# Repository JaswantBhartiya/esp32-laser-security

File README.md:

<div align="center">

  <br><br>

<br><br>

# 🛡️ ESP32 Multi-Bounce Laser Security System
<!-- Badges Section -->
<p align="center">

</p>

<h4>
    <a href="#demo">Demo</a>&nbsp;&nbsp;&nbsp;&nbsp;•&nbsp;&nbsp;&nbsp;&nbsp;
    <a href="#hardware">Hardware Design</a>&nbsp;&nbsp;&nbsp;&nbsp;•&nbsp;&nbsp;&nbsp;&nbsp;
    <a href="#mechanical">Mechanical Shroud</a>&nbsp;&nbsp;&nbsp;&nbsp;•&nbsp;&nbsp;&nbsp;&nbsp;
    <a href="#firmware">Firmware & Calibration</a>&nbsp;&nbsp;&nbsp;&nbsp;•&nbsp;&nbsp;&nbsp;&nbsp;
    <a href="https://github.com/JaswantBhartiya" target="_blank">Contact</a>
</h4>
</div>

<br>

A professional, budget-friendly embedded security system built around a custom PCB and the ESP32 DevKit V1. This project utilizes an optical multi-bounce laser path bounced across real glass mirrors to form a tight perimeter grid, monitored dynamically by an onboard Light Dependent Resistor (LDR).

<br><br>

---

## <span id="demo">🚀</span> Key Features & Demo

* **Wireless Perimeter Design:** The laser operates on its own isolated battery across the room, eliminating long, messy signal lines back to the controller.
* **Multi-Bounce Path:** Supports $650\text{nm}$ red or $532\text{nm}$ green lasers, holding a sharp focal point through 4 to 5 mirror reflections.
* **Auto Ambient Calibration:** Samples room light on boot to calculate a dynamic trigger threshold, preventing false alarms from day to night.
* **Dual-State LED Status:** Uses a Red-Green LED array (**Green** for Armed, **Red** for Tripped) mirrored on both the board and an external header.
* **Hardware Reset Button:** A debounced button on `GPIO 18` instantly clears the alarm, silences the buzzer, and re-arms the system.

<br>

### 🖥️ Live Web UI Dashboard
The system hosts a real-time responsive dashboard providing live telemetry, node statuses, and toggle configurations.

| Central Telemetry Instrumentation | Edge Sensor Matrix Nodes |
| :---: | :---: |
|  |  |

#### 🌐 Robust 6-Way Connection Matrix
To guarantee fail-safe alerts and zero telemetry loss, the firmware maintains six independent network connections across local and global layers:
* **Wi-Fi Link Status:** Dual-channel monitoring covering your local gateway routing (`HTTP-Local`) and direct internet access (`HTTP-Router`).
* **MQTT Brokers:** Redundant pub/sub data streams routed concurrently to an offline network broker (`MQTT-Local`) and a remote cloud cluster (`MQTT-Cloud`).
* **Ntfy Push Alerts:** High-priority notification pipelines feeding instant breach logs via a self-hosted instance (`NTFY-Local`) and a global web server (`NTFY-Global`).

<br>

---

## <span id="hardware">🛠️</span> Hardware Design

### System Schematic
The circuit diagram maps out the ESP32 interface, sensor voltage dividers, and laser control lines for low-noise operation.

<br>

### 📐 Electronics Layout (Raw KiCad PCB)
The custom board features a compact form factor, dedicated mounting holes, and clear silkscreen labeling.

| Front Layout | Back Layout |
| :---: | :---: |
|  |  |

<br>

### <span id="mechanical"></span>⚙️ Standalone Mechanical Mount
To achieve complete optical isolation and filter out ambient environmental light, a custom-molded mounting shroud was engineered.
<details> 
<summary><b>Click to Expand | Standalone Shroud Views</b></summary>

<br>

| Isometric View | Front View | Back View |
| :---: | :---: | :---: |
|  |  |  |

#### 📐 Engineering Dimensions & Tolerances

**Design Specifications:**

* **Material:** Matte/Satin Dark Grey PLA (To absorb stray internal reflections)
* **Internal Diameter:** Uniform 5.7mm corridor (Provides a 0.5mm clearance cushion for hand-soldered LDR play and FDM printing shrinkage)
* **Fasteners:** Dual M3 clearance holes for flush mounting.

</details>

<br>

👉 **[Click here to view the interactive 3D Mount Model Natively on GitHub](./production/3d_printing/mount.STL)**

<br>

### 🤝 Fully Integrated Assembly
The combined views show the mechanical shroud assembly bolted directly onto the electronic control circuit board.

<div align="center">
       
</div>

<br>
       
| Assembly Top View | Assembly Solder Side View |
| :---: | :---: |
|  |  |

<br>

---

## 🔋 Power Setup

<details>
  
<summary><b>Click to Expand | Power Setup for two Paths</b></summary>

<br>

The system uses **two separate power paths** to stop electrical noise from the laser from messing with the ESP32 and sensors.

### ⚡ Path 1: ESP32 & Custom PCB
Powers the main controller and sensor board.

<div align="center">
       
</div>

<br>

* **Battery (18650)** ➔ **TP4056 Charger** (Safe charging)
* **TP4056 Output** ➔ **Boost Converter** (Steps up voltage)
* **Boost Converter (5V)** ➔ **ESP32 Pin (5V)** (Powers MCU)
* **ESP32 Pin (3.3V)** ➔ **Custom PCB (J2)** (Powers LDR & LED)

<br>

### 🔦 Path 2: Standalone Laser Transmitter Node
Powers the laser module independently with zero physical connection to the main board.

<div align="center">
    
</div>

<br>

* **100% Isolated:** No shared wires or common ground loops with the ESP32-S3.
* **18650 Battery Powered:** Runs on its own 18650 cell (~3.7V) for maximum, long-lasting brightness.
* **Manual Switch Control:** Uses an inline rocker switch to completely cut power and save battery when off.

</details> 

<br>

---

## 📂 Repository Structure
``` yaml
      esp32-laser-security/
      ├── src/                             # 💻 Firmware Source Code (PlatformIO)
      │   ├── main.cpp                     #   └── Main security system logic
      │   └── testing/                     #   └── Isolated hardware testing scripts
      │       └── laser-connected-esp.cpp
      │
      ├── esp32-laser-security-pcb/        # 🛠️ KiCad Hardware Design Files
      │   ├── *.kicad_sch                  #   └── Circuit schematic
      │   └── *.kicad_pcb                  #   └── PCB routing layout
      │
      ├── production/                      # 📦 Manufacturing & 3D Printing Files
      │   ├── gerbers/                     #   └── PCB manufacturing files (Gerbers)
      │   ├── 3d_printing/                 #   └── 3D-printable mount shroud (.STL / .3MF)
      │   └── step_models/                 #   └── 3D CAD assembly model (.STEP)
      │
      ├── assets/                          # 🖼️ Documentation Media
      │   ├── circuit_schematic.png        #   └── Circuit diagram for README
      │   ├── pcb_raw_*.png/jpg            #   └── 3D images of unmounted PCB
      │   ├── mount_*.jpg                  #   └── 3D images of standalone plastic mount
      │   └── pcb_assembled_*.jpg          #   └── Photos of the final assembly
      │
      ├── platformio.ini                   # ⚙️ Project configuration & libraries
      └── README.md                        # 📖 Main project documentation guide
```
<br>

---

## 🛠️ Hardware Requirements

| Component | Quantity | Purpose |
| :--- | :--- | :--- |
| **ESP32-S3 DevKitC-1 N16R8** | 1 | Central processing unit & real-time monitoring engine |
| **SYD1230 650nm 5mW Red Laser Module** | 1 | Focusable transmitter node optimized for budget-friendly bouncing |
| **Light Dependent Resistor (LDR)** | 1 | High-sensitivity optical receiver |
| **SFM-27 Active Piezo Buzzer (Continuous Sound)** | 1 | 3–24V high-decibel audible indicator; allows the ESP32 to cleanly drive custom dual-frequency police siren sweeps without internal timing conflicts |
| **First-Surface Mirrors / HDD Platters** | 2–4 | Zero-ghosting high-reflectivity corner reflection nodes |
| **Metal Film Resistor (10 kΩ)** | 1 | Pull-down resistor for the analog voltage divider circuit |
| **Metal Film Resistor (330 Ω)** | 2 | Current-limiting protection resistors (e.g., for status LEDs) |
| **Metal Film Resistor (220 Ω)** | 2 | Current-limiting protection resistors (e.g., for buzzer power constraints) |
| **6x6x5mm Tactile Push Button Switch** | 1 | PCB-mount tactile switch for instant manual system reset or calibration |
| **7×1 Pin Male Berg Header (Straight, 10mm Height, 2.54mm Pitch)** | 1 | Breakout interface connector for peripheral GPIO programming/debugging pins |
| **XY126V-5.0-2P Green Screw Terminal Block (5mm Pitch, Through Hole)** | 1 | XINLAIYA 10A 300V power connector with wire protection for external main DC input |
| **3 Pin JST XH 2.5mm Top Entry Header (Straight Male & Female Pair)** | 1 | Polarity-keyed locking connector for secure LDR receiver wire routing |
| **Socket Head Cap Screw (M3x12)** | 2 | High-strength mechanical fasteners for enclosure or PCB corner mounting |
| **M3 Stainless Steel Hex Nut** | 2 | Matching rust-resistant hexagonal nuts to secure the M3 mounting screws safely |

<br>

---

## 🔌 Circuit Topology & Wiring

To achieve a clean optical baseline and prevent room lighting from flooding the sensor, the LDR must be housed inside an opaque, dark isolation tube pointed directly down the incoming laser path.

### Central Control Unit Pinout Mapping

```text
      +-----------------------------------------------------------------+
      |                    ESP32-S3 DevKitC-1 N16R8                     |
      +-----------------------------------------------------------------+
        | GPIO 4 (ADC) | <-------> Pin 1: LDR  (R1 Sensor Output Node)
        | GPIO 18       | <-------- Pin 2: RST  (Reset Push Button SW1)
        | GPIO 5        | --------> Pin 3: BUZZ (External Buzzer J3)
        | GPIO 19*      | --------> Pin 4: GRN  (Green LED Control Rail)
        | GPIO 21*      | --------> Pin 5: RED  (Red LED Control Rail)
        | GND           | --------> Pin 6: GND  (Common System Ground)
        | 3V3           | --------> Pin 7: 3V3  (System Power Input)

```
``` text
        +-----------------------------------------------------------------------------------+
        |                            EXTERNAL COMPONENT CONNECTIONS                         |
        +-----------------------------------------------------------------------------------+
        |                                                                                   |
        |  [ PCB Header J1 ] --------------------> Connects to EXTERNAL RG LED              |
        |     (EXT. RG LED)                         - Pin R: Red Indicator Anode            |
        |                                           - Pin G: Green Indicator Anode          |
        |                                           - Pin -: Common Ground Rail             |
        |                                                                                   |
        |  [ PCB Header J3 ] --------------------> Connects to EXTERNAL ACTIVE BUZZER       |
        |     (EXT. BUZZER)                         - Pin +: Positive Audio Signal Input    |
        |                                           - Pin -: Negative Ground Return         |
        |                                                                                   |
        +-----------------------------------------------------------------------------------+

```

### 3.3V Safe Voltage Divider Layout

```text
3V3 Rail -----[ LDR ]-----+-----> GPIO 34 (Analog Read Input)
                          |
                     [ 10kΩ Resistor ]
                          |
                         GND Rail
```
_Note: Powering the LDR network from the 3V3 rail protects the ESP32's 12-bit ADC pins from 5V over-voltage degradation._

<br>

---

## 💻 Software Configuration & Installation

This project is built using PlatformIO IDE inside VS Code for robust environment management and smaller, compiled binary footprints.
### Project Environment Configuration (platformio.ini)

```Ini, TOML

[env:esp32-s3-devkitc-1]
platform = espressif32
board = esp32-s3-devkitc-1
framework = arduino
monitor_speed = 115200

# Force the compiler to disable PSRAM tracking to prevent boot panics
build_flags = 
    -DBOARD_HAS_PSRAM=0
    -DARDUINO_USB_CDC_ON_BOOT=1

# Specify LittleFS partitioning layout
board_build.filesystem = littlefs

# Standard partition table for an 8MB Flash device (No PSRAM)
board_build.partitions = default_8MB.csv

lib_deps =
    esphome/ESPAsyncWebServer-esphome @ ^3.2.2
    knolleary/PubSubClient @ ^2.8

# Tell PlatformIO to compile everything in src, EXCEPT the testing folder
build_src_filter = +<*> -<testing/>

```
<br>

### Deployment Instructions

1. Clone this repository to your local workspace:
    ```Bash
    git clone https://github.com/JaswantBhartiya/esp32-laser-security.git
    ```
    
2. Open the project folder directly inside **Visual Studio Code** with the **PlatformIO** extension active.

3. Align your external laser node across your mirror grid so it hits the center of the LDR tube.

4. Click the **PlatformIO**: **Upload** arrow icon on the bottom status bar (or press (`Ctrl + Alt + U`) to compile and flash the firmware.

5. Open the **Serial Monitor** (`Ctrl + Alt + M`) at `115200` baud to watch the system run its initial calibration profiling.
<br><br>

---

## ⚙️ How System States Work

```text
  
           +------------------+
           | STATE_CALIBRATING| <-------- On Boot / User Reset
           +------------------+
                     |
                     v (Samples light & computes threshold)
           +------------------+
      +--->|   STATE_ARMED    |
      |    +------------------+
      |              |
      |              v (Beam broken for >50ms)
      |    +------------------+
      |    |  STATE_BREACHED  |
      |    +------------------+
      |              |
      +--------------+ (Reset Button Pressed)

```

* **Boot Calibration:** Samples the laser beam for 3 seconds to calculate a dynamic trigger threshold between direct laser light and ambient room light.
* **Active Guard:** Continuously samples the LDR. Requires the beam to be broken for over `50ms` to filter out false alarms from dust or bugs.
* **Breached Alert:** Plays a dual-tone siren sweep ($800\text{Hz}$ to $1300\text{Hz}$) on `GPIO 5` using non-blocking microsecond delays.
* **Hardware Reset:** Actively polls `GPIO 18`. Pressing the reset button instantly mutes the buzzer and recalibrates the system back to Armed mode.

<br>

---

## ⚙️ Calibration & Environment Tuning

### 🛠️ Quick Alignment Guide

1. **Align:** Aim the laser dot directly into the center of the LDR shroud.
2. **Calibrate:** Power on or reset the ESP32. Keep the laser path completely clear for the first **3 seconds**.
3. **Calculate:** The firmware auto-sets the trigger threshold using a simple median formula:

$$\text{Threshold} = \frac{\text{Laser Intensity} + \text{Ambient Light}}{2}$$

4. **Verify:** Block the beam with your hand to test that it instantly triggers the alarm.

<br>

### 🔍 Ambient Light Troubleshooting

| Issue | Root Cause | Quick Fix |
| :--- | :--- | :--- |
| **Instant alarm on boot** | Laser missed the LDR during calibration. | Re-align the laser and press the reset button to recalibrate. |
| **Beam broken, no alarm** | Side-glare or ambient room light is bleeding into the sensor. | Move away from windows or use a longer 3D-printed shroud to block ambient light. |
| **Siren flickers/jitters** | Laser dot is slightly misaligned or vibrating on the edge of the sensor. | Tighten your laser/mirror mounts to eliminate physical jitter. |

<br>

---

## 🚀 Hardware Evolution & Development
To see the complete multi-phase development timeline—including planned v2.0 hardware protection circuits, v3.0 wireless IoT feature tracking, and long-term mechanical upgrades—view the project's growth pipeline:

👉 **[View the Comprehensive Project Roadmap & Future Upgrades](./HARDWARE_ROADMAP.md)**

<br>

---

## 📄 License

This project is licensed under the MIT License - see the [`LICENSE`](./LICENSE) file for details.

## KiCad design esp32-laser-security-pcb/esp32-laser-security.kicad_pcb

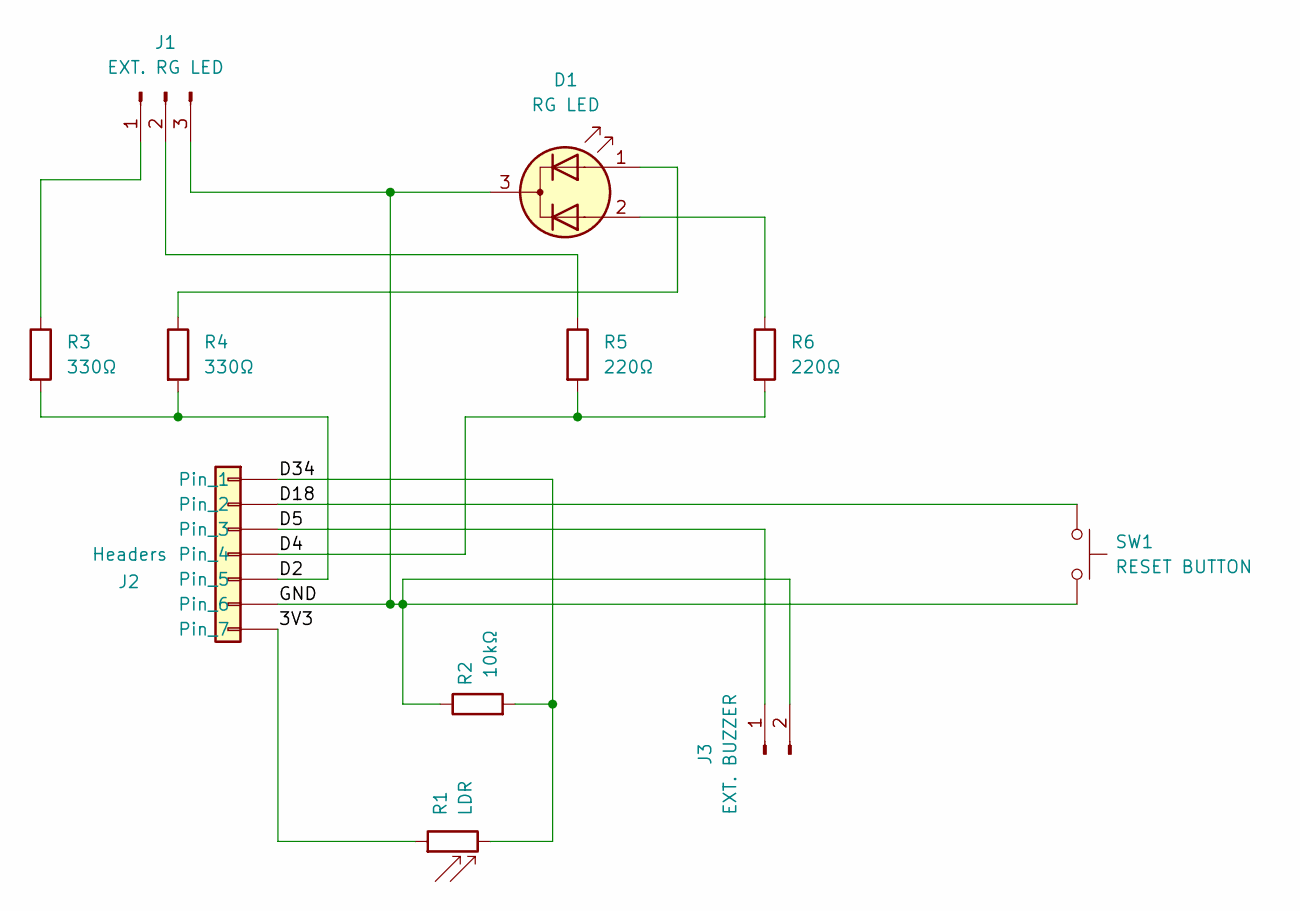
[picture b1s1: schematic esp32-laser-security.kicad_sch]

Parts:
D1: RG LED; LED_D5.0mm-3
J1: EXT. RG LED; JST_XH_B3B-XH-AM_1x03_P2.50mm_Vertical
J2: Headers; PinHeader_1x07_P2.54mm_Vertical
J3: EXT. BUZZER; TerminalBlock_MaiXu_MX126-5.0-02P_1x02_P5.00mm
R1: LDR; R_LDR_5.1x4.3mm_P3.4mm_Vertical
R2: 10kΩ; R_Axial_DIN0207_L6.3mm_D2.5mm_P7.62mm_Horizontal
R3, R4: 330Ω; R_Axial_DIN0207_L6.3mm_D2.5mm_P7.62mm_Horizontal
R5, R6: 220Ω; R_Axial_DIN0207_L6.3mm_D2.5mm_P7.62mm_Horizontal
SW1: RESET BUTTON; SW_PUSH_6mm

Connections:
/3V3: J2.7, R1.1
/D2: J2.5, R3.2, R4.2
/D4: J2.4, R5.2, R6.2
/D5: J2.3, J3.1
/D18: J2.2, SW1.1
/D34: J2.1, R1.2, R2.2
/GND: D1.3 (K), J1.3, J2.6, J3.2, R2.1, SW1.2
unnamed: D1.1 (A1), R4.1
unnamed: D1.2 (A2), R6.1
unnamed: J1.1, R3.1
unnamed: J1.2, R5.1

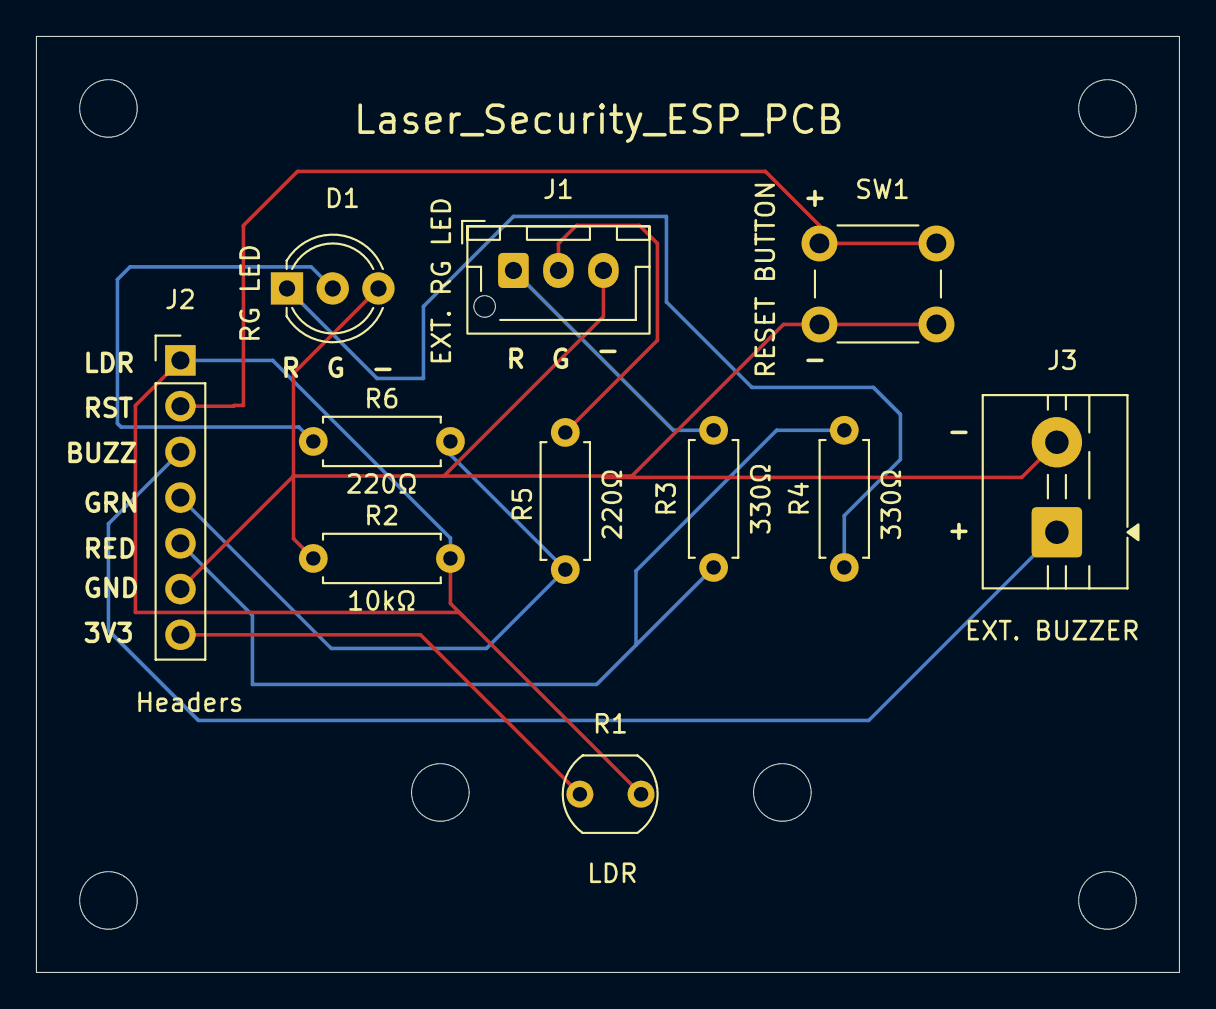
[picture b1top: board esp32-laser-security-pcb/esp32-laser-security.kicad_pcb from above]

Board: 2 copper layers, 63.5 x 52.0 mm, 11 parts (0 on the bottom side), 11 nets.

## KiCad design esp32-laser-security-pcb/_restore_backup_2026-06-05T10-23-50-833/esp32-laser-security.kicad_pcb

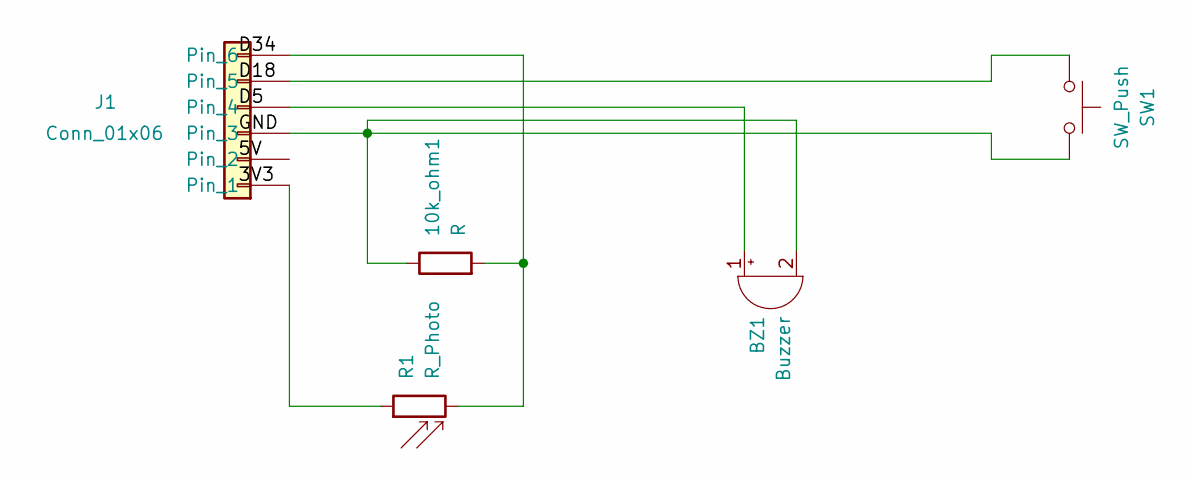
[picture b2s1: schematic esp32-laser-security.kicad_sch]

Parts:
10k_ohm1: R; R_Axial_DIN0207_L6.3mm_D2.5mm_P7.62mm_Horizontal
BZ1: Buzzer; Buzzer_12x9.5RM7.6
J1: Conn_01x06; PinHeader_1x06_P2.54mm_Vertical
R1: R_Photo; R_LDR_5.1x4.3mm_P3.4mm_Vertical
SW1: SW_Push; SW_PUSH_6mm

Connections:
unnamed: BZ1.1 (+), J1.4
unnamed: 10k_ohm1.1, BZ1.2 (-), J1.3, SW1.2
unnamed: J1.1, R1.1
unnamed: J1.5, SW1.1
unnamed: 10k_ohm1.2, J1.6, R1.2

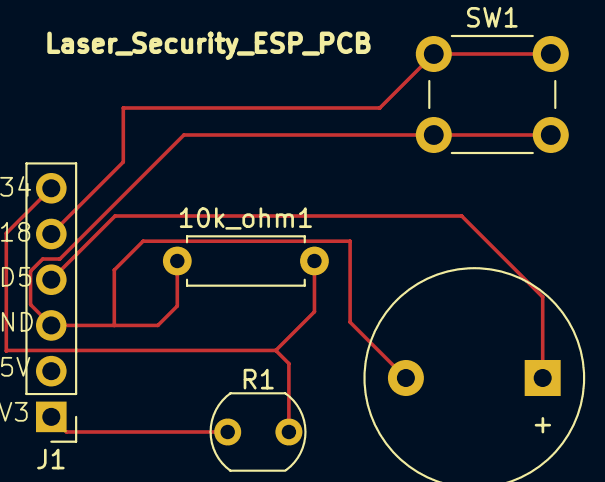
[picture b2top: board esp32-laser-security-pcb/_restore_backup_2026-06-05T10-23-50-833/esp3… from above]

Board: 2 copper layers, 5 parts (0 on the bottom side), 5 nets.

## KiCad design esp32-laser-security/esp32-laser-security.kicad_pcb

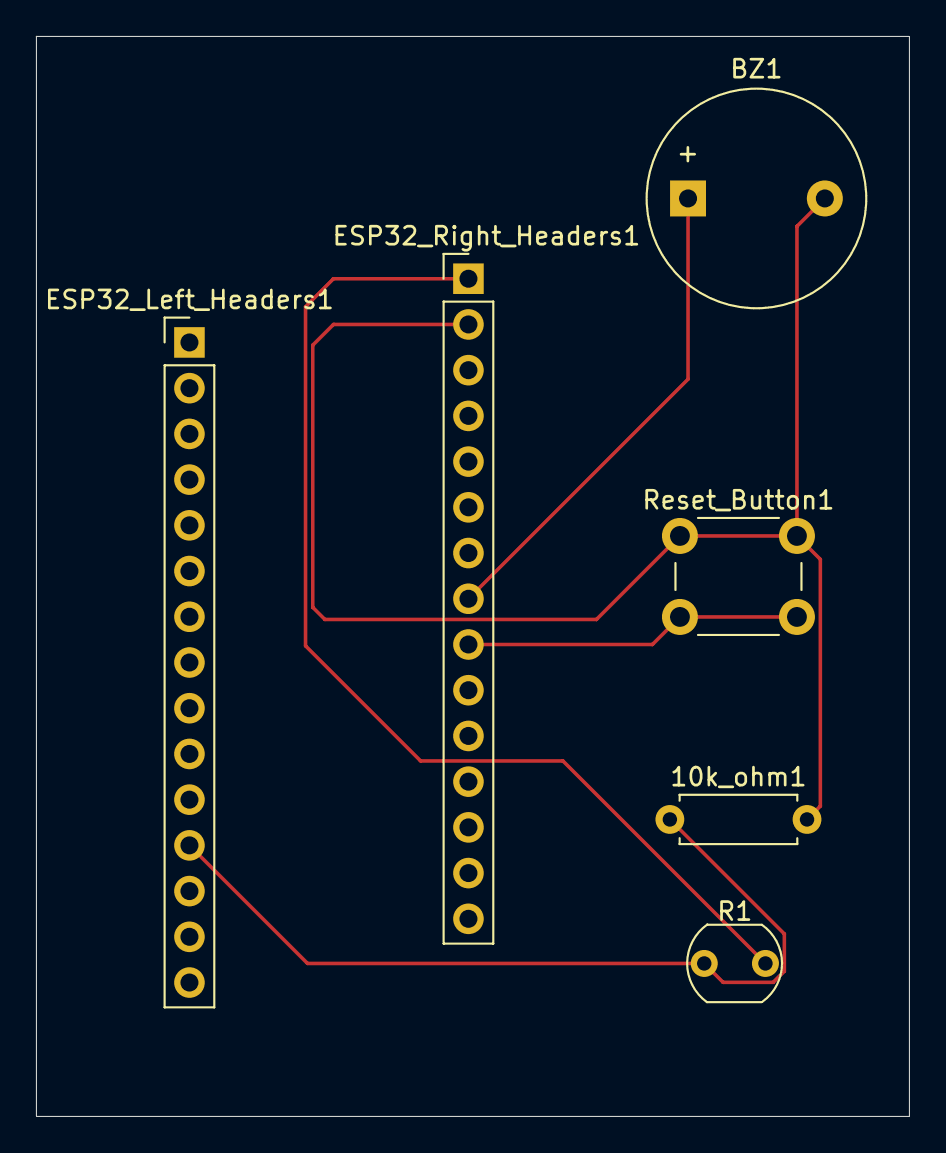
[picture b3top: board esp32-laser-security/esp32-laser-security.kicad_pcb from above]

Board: 2 copper layers, 48.5 x 60.0 mm, 6 parts (0 on the bottom side), 5 nets.

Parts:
10k_ohm1: R; R_Axial_DIN0207_L6.3mm_D2.5mm_P7.62mm_Horizontal
BZ1: Buzzer; Buzzer_12x9.5RM7.6
ESP32_Left_Headers1, ESP32_Right_Headers1: Conn_01x15_Pin; PinHeader_1x15_P2.54mm_Vertical
R1: R_Photo; R_LDR_5.1x4.3mm_P3.4mm_Vertical
Reset_Button1: SW_Push; SW_PUSH_6mm

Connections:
unnamed: BZ1.1 (+), ESP32_Right_Headers1.8
unnamed: 10k_ohm1.2, BZ1.2 (-), ESP32_Right_Headers1.2, Reset_Button1.1
unnamed: 10k_ohm1.1, ESP32_Left_Headers1.12 (Pin_12_12), R1.1
unnamed: ESP32_Right_Headers1.1, R1.2
unnamed: ESP32_Right_Headers1.9, Reset_Button1.2

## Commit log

2026-06-04 Initial commit: Streamlined independent laser architecture with jumper reset
2026-06-04 Initialize README with project details and setup
    Added detailed project documentation for the Independent Long-Range Multi-Bounce Laser Security System, including features, hardware requirements, circuit topology, and software configuration.
2026-06-04 Refactor: organize source directories and update build_src_filter configuration
2026-06-04 Added Kicad Schematic & PCB Design
2026-06-04 changed pcb folder name
2026-06-04 corrected .gitignore
2026-06-05 Updated pcb design and add schematic and 3D PCB render images for laser security board
2026-06-05 removed unnecessary old files
2026-06-05 added gerber files
2026-06-05 Revise README.md for repository structure and clarity
    Updated repository structure and improved formatting in README.md for clarity.
2026-06-06 added mount & updated pcb
2026-06-06 Revise README for hardware design details and images
    Updated hardware design section with new PCB and mount images, and improved layout descriptions.
2026-06-06 Update README.md to fix formatting issue
    Removed unnecessary code block formatting from repository structure section.
2026-06-06 Add system schematic to README
    Added a section for the system schematic with a diagram.
2026-06-06 added mount dimension sheet
2026-06-08 updated pcb
2026-06-08 updated pcb schematic and gerber files for industry
2026-06-08 Add MIT License to the project
2026-06-08 Revise PCB layout presentation in README
    Updated PCB layout images and enhanced formatting for clarity.
2026-06-08 Refactor README for improved clarity and formatting
    Removed unnecessary line breaks and improved formatting in the README.
2026-06-08 updated mount files
2026-06-08 Revise view labels and update image references
    Updated images and descriptions for views in the README.
2026-06-09 Update README.md for improved clarity and structure
2026-06-09 Add hardware hardening and optimization roadmap
    Document hardware modifications for the Laser Security ESP PCB to enhance reliability and performance in room-scale deployments, addressing vulnerabilities and implementing protective measures.
2026-06-09 Expand hardware roadmap with mechanical design details
    Added detailed sections on mechanical mounts and enclosure design for future revisions, including micro-adjustable mirror alignment mounts, decentralized external LED panels, and high-acoustic extern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
2026-06-09 Revise Active Piezo Buzzer description in README
    Updated the description of the Active Piezo Buzzer to specify its continuous sound capability and voltage range.
2026-06-10 added web ui for both home router and local esp wifi
2026-06-10 Add HTML5, CSS3, JavaScript, and ESP32-S3 badges
2026-06-10 Add .gitattributes to track frontend files
2026-06-12 Update ESP32 badge in README
2026-06-12 making new software with typescript & corrected .html and .ts
2026-06-12 Add TypeScript badge to README
    Added TypeScript badge to the README.
2026-06-13 Add JavaScript badge to README
2026-06-17 build js from updated ts file
2026-06-18 added powering pcb and esp section
2026-06-18 Update README with laser transmitter path
2026-06-18 added fritzing project with parts
2026-06-18 Clean up README by removing esp32dev config
    Removed commented configuration for esp32dev environment.
2026-06-20 Revise README.md for feature descriptions and clarity
    Updated key features and system state descriptions in README.md for clarity and consistency.
2026-06-20 added laser power suply fritzing project
2026-06-20 rename image file name in assets
2026-06-26 Enhance README with power setup details
    Added detailed power setup section with two paths for ESP32 and sensors.
2026-06-26 Enhance .gitignore with additional ignore patterns
    Updated .gitignore to include new ignore patterns for PlatformIO, VS Code, local history, and test folders.
2026-06-26 Enhance README with web UI and connection matrix info
    Added details about the live web UI dashboard and connection matrix.
2026-06-26 add: webui-dashboard image in readme.md
2026-06-27 update: webui-dashboard.png
2026-06-28 Enhance README with image and table updates
    Updated README to improve image formatting and added a table for telemetry instrumentation.
2026-06-28 Increase image widths in README table
    Updated image widths in the README for better visibility.

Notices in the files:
README.md:
License: MIT
